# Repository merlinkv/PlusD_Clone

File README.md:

# PlusD Clone

<br />This work is licensed under a <a rel="license" href="http://creativecommons.org/licenses/by-nc-sa/4.0/">Creative Commons Attribution-NonCommercial-ShareAlike 4.0 International License</a>.

* If you remix, transform, or build upon the material, you must distribute your contributions under the same license as the original.
* You may not use the material for commercial purposes.
* You must give appropriate credit, provide a link to the license, and indicate if changes were made. You may do so in any reasonable manner, but not in any way that suggests the licensor endorses you or your use.

This interface is based on the original PlusD (+D) interface from Miles Gordon Technology and the clone designs by @Pachuquin & @alvaroalea.

# ATTENTION

This project was made for the retro community and not for commercial purposes. So only retro hardware forums and individual people can build this project.

THE SALE OF ANY PART OF THIS PROJECT ON EBAY OR OTHER AUCTION SITES IS PROHIBITED

# Note

I take no responsibiltiy for any damage to any equipment that results from the use of this board. USE AT YOUR OWN RISK!

# Original short description

The PlusD (or +D) was a floppy disk and printer interface for the Sinclair ZX Spectrum home computer, developed as a successor to Miles Gordon Technology's earlier product, the DISCiPLE. It runs the GDOS or Uni-Dos operating systems and you can connect up to two 3.5" floppy drives.

The PlusD will allow you to save all your games and serious software to disc at the touch of a button for reloading at any time in the future. With the fastest load and
save times of any disc system available for the Spectrum, the PLUS D will make your computer grow to meet your needs today and tomorrow! In the software arena, many
leading companies are now producing software that is specifically tailored to the PLUS D. But don't worry - you don't have to buy new software to use the PLUS D!
And if some of your software is Microdrive compatible, so much the better! The PLUS D will add a new dimension to all your existing software, greatly enhancing all
your own programs as well!

# August 6, 2025 - PlusD Clone 1.7

* Added Fire2 button on Kempston interface. Now you can play games that are ready for two buttons or modified to add this possibility like on some games modded by @mad3001 at the VDR site: [Games with Fire2](https://www.va-de-retro.com/foros/viewtopic.php?t=12277)

- [Interactive BOM](https://htmlpreview.github.io/?https://github.com/merlinkv/PlusD_Clone/blob/master/ZX_PlusD_Clone_1_7.html)

# PlusD Clone 1.6

My ZX PlusD Clone can be used on all ZX Spectrum computers just using a little switch (you don't need a "fixer" for +2A, +2B or +3 models). Also you can select one of the two ROMs included (GDOS & Uni-Dos -up to four ROMs can be used-) and play almost all games with the integrated Kempston Joystick interface.

# July 30, 2021

* Corrected some IC labels on the board.

# November 25, 2020

* The solder pad used to select the floppy drive controller IC has been removed.
The floppy drive controller IC's that can be used are: WD1772-02-00, WD1772-02-02 & VL1772-02PC
* Some minor changes.

# October 16, 2020

* Resistors, capacitors (except the two electrolytics) & diodes now are SMD 1206
* Some minor changes

# September 25, 2020

* In this version the solder pads to select the READY signal has been removed.
* Now you can fin a connector of 4x2 pins to put the jumpers.
     
     * Upper row: Cable selector (AT or Shugart)
     * Bottom row: READY signal selector, REAL or EMU
      
     See attached pictures.

# July 27, 2020

Tested & working 100%
* In this version of the board the IC 7805 has been removed. The interface power is taken from the + 5V line of the expansion bus.

# July 11, 2020

* Corrected footprint of U2 (W27E257)
* Everything seems to be OK. Ordering 5 PCB's to test.

# July 6, 2020

* Added a SPDT switch ON-ON to select between ZX 48K/128K & +2A/+3
* Inversion of Drive 1 and Drive 2 now is made by a DPDT Switch (ABBA)
* Now the IC12 (L7805) can be placed horizontally
* Relocation of LEDS, NMI and RESET pushbuttons and some IC's
* Added three 3M holes (3.5mm) to facilitate the fixation on a case
* Kempston Joystick connector now is horizontal
* Changed the DIP switch for ROM selection and Joystick ON-OFF for a DIP Switch Piano style.
* Electrolytic capacitors are now SMD

# Notes

Two types can be used as the IC for floppy disk controller: WD1772 (versions 02-00 and 02-02) and VL1772-02PC.
Unfortunately, they are difficult to find at reasonable prices.

The advantages of this interface over the original are:

* 4 Banks of ROM, so you can swap between G+Dos and Unidos, selectable by dip-switches
* Included Fixed for +2A/+3, so can be used in any ZX Spectrum, selection by switch
* Kempston Joystick Interface included, can be disable by dip-switch
* Reset Button
* Posibility of use crossed or plain floppy cable, and invert Drive 1 and Drive 2, very usefull if you have a Gotek and a real floppy.

# Links

* https://www.winuaespanol.com/phpbb3/viewtopic.php?p=7182#p7182
* https://github.com/alvaroalea/plusD-clone
* https://www.va-de-retro.com/foros/viewtopic.php?f=63&t=5561

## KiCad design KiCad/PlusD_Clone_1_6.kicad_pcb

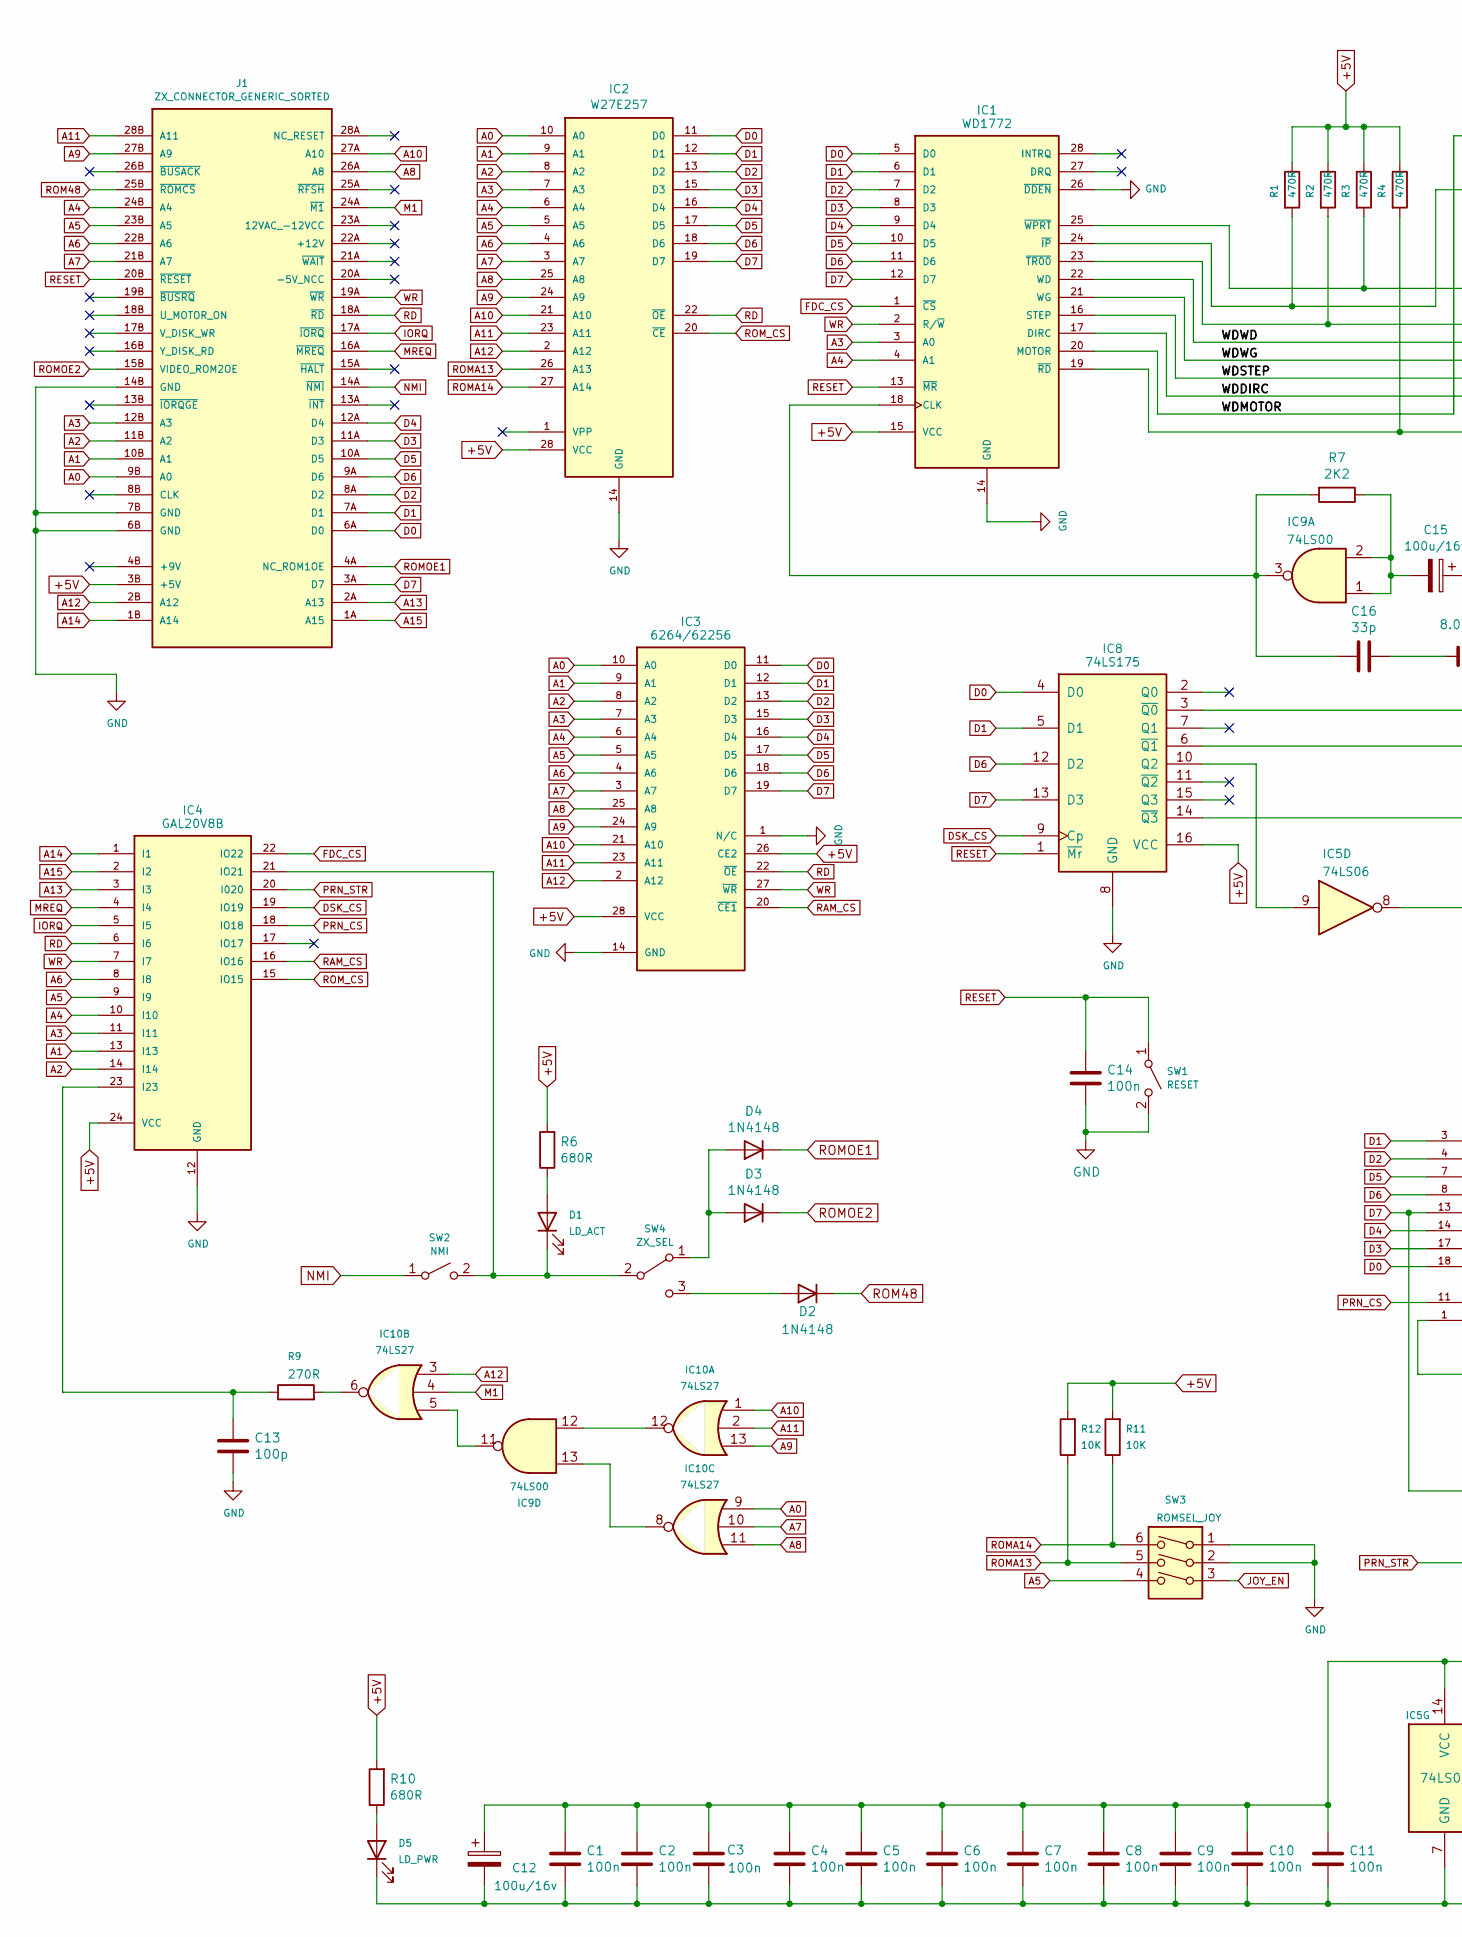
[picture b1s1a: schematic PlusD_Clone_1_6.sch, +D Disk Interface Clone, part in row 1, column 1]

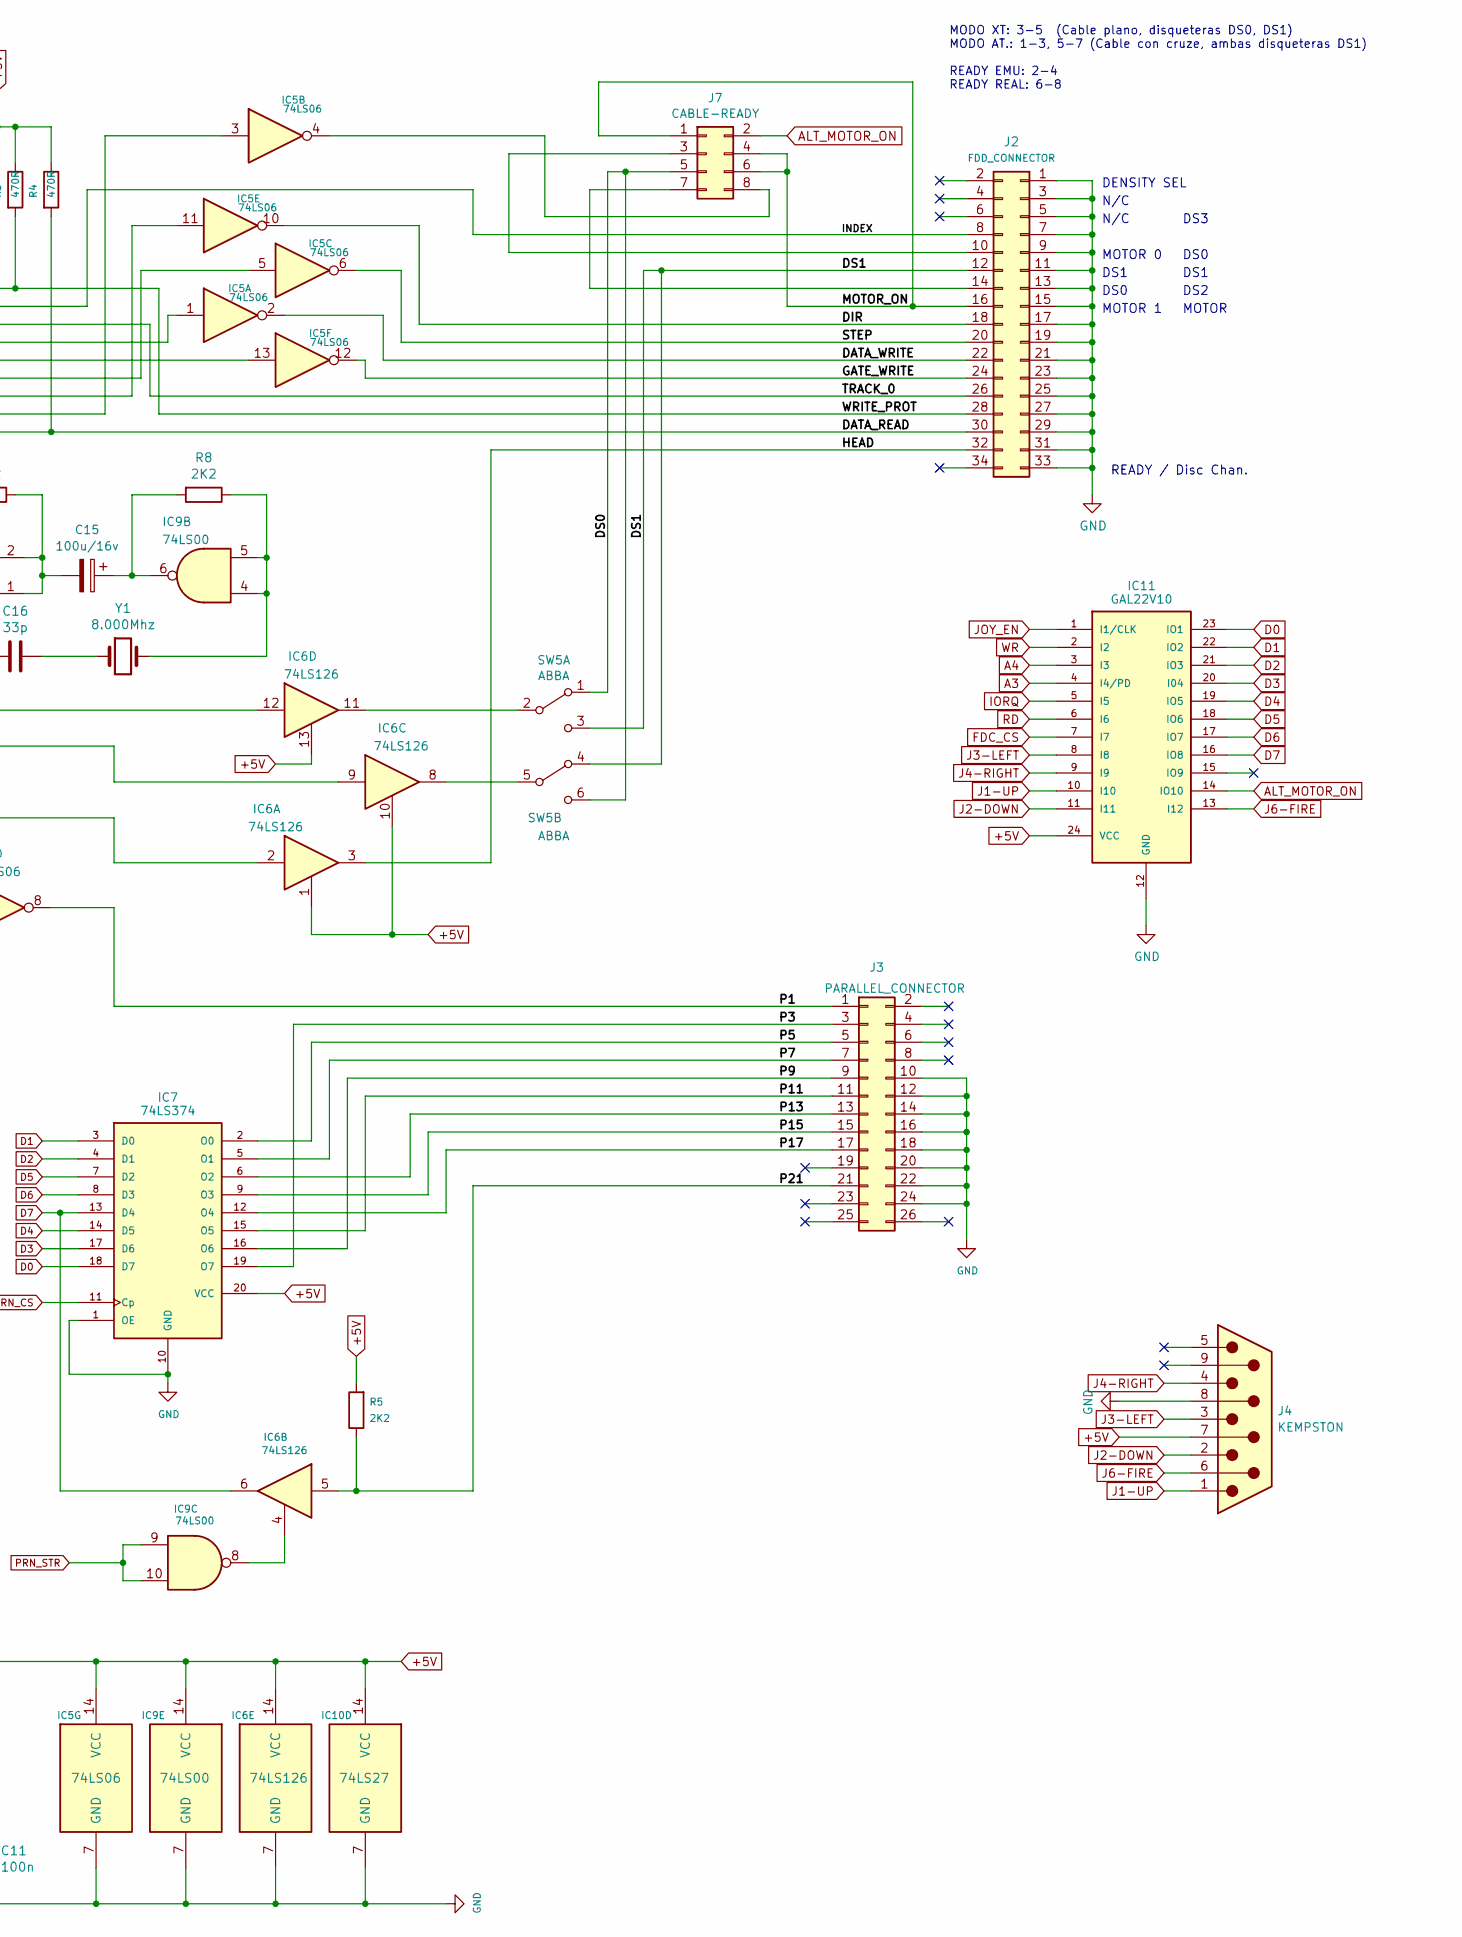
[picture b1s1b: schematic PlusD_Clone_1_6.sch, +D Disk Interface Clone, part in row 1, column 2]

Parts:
C1, C2, C3, C4, C5, C6, C7, C8, C9, C10, C11, C14: 100n; C_1206_3216Metric_Pad1.42x1.75mm_HandSolder
C12, C15: 100u/16v; C_Elec_6.3x5.4
C13: 100p; C_1206_3216Metric_Pad1.42x1.75mm_HandSolder
C16: 33p; C_1206_3216Metric_Pad1.42x1.75mm_HandSolder
D1: LD_ACT; LED_D5.0mm
D2, D3, D4: 1N4148; D_SOD-123
D5: LD_PWR; LED_D5.0mm
IC1: WD1772; DIP-28_W15.24mm_Socket_LongPads
IC2: W27E257; DIP-28_W15.24mm_Socket_LongPads
IC3: 6264/62256; DIP-28_W15.24mm_Socket_LongPads
IC4: GAL20V8B; DIP-24_W7.62mm_Socket_LongPads
IC5: 74LS06; DIP-14_W7.62mm_Socket_LongPads
IC6: 74LS126; DIP-14_W7.62mm_Socket_LongPads
IC7: 74LS374; DIP-20_W7.62mm_Socket_LongPads
IC8: 74LS175; DIP-16_W7.62mm_Socket_LongPads
IC9: 74LS00; DIP-14_W7.62mm_Socket_LongPads
IC10: 74LS27; DIP-14_W7.62mm_Socket_LongPads
IC11: GAL22V10; DIP-24_W7.62mm_Socket_LongPads
J1: ZX_CONNECTOR_GENERIC_SORTED
J2: FDD_CONNECTOR; PinHeader_2x17_P2.54mm_Vertical
J3: PARALLEL_CONNECTOR; PinHeader_2x13_P2.54mm_Vertical
J4: KEMPSTON; DSUB-9_Male_Horizontal_P2.77x2.84mm_EdgePinOffset4.94mm_Hou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
J7: CABLE-READY; PinHeader_2x04_P2.54mm_Horizontal
R1, R2, R3, R4: 470R; R_1206_3216Metric_Pad1.42x1.75mm_HandSolder
R5, R7, R8: 2K2; R_1206_3216Metric_Pad1.42x1.75mm_HandSolder
R6, R10: 680R; R_1206_3216Metric_Pad1.42x1.75mm_HandSolder
R9: 270R; R_1206_3216Metric_Pad1.42x1.75mm_HandSolder
R11, R12: 10K; R_1206_3216Metric_Pad1.42x1.75mm_HandSolder
SW1: RESET; SW_PUSH_6mm
SW2: NMI; SW_PUSH_6mm
SW3: ROMSEL_JOY; SW_DIP_SPSTx03_Piano_10.8x9.18mm_W7.62mm_P2.54mm
SW4: ZX_SEL; SW_CuK_OS102011MA1QN1_SPDT_Angled
SW5: ABBA; SW_CuK_JS202011AQN_DPDT_Angled
Y1: 8.000Mhz; Crystal_HC18-U_Vertical

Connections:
+5V: C1.2, C2.2, C3.2, C4.2, C5.2, C6.2, C7.2, C8.2, C9.2, C10.2, C11.2, C12.1, IC1.15 (VCC), IC2.28 (VCC), IC3.26 (CE2), IC3.28 (VCC), IC4.24 (VCC), IC5.14 (VCC), IC6.1, IC6.10, IC6.13, IC6.14 (VCC), IC7.20 (VCC), IC8.16 (VCC), IC9.14 (VCC), IC10.14 (VCC), IC11.24 (VCC), J1.3B (+5V), J4.7, R1.1, R2.1, R3.1, R4.1, R5.2, R6.2, R10.2, R11.2, R12.2
/DATA_READ: IC1.19 (~RD), J2.30, R4.2
/DATA_WRITE: IC5.2, J2.22
/DIR: IC5.10, J2.18
/DS0: J7.5, SW5.1 (A), SW5.6 (C)
/DS1: J2.12, SW5.3 (C), SW5.4 (A)
/GATE_WRITE: IC5.12, J2.24
/HEAD: IC6.3, J2.32
/INDEX: IC1.24 (~IP), J2.8, R1.2
/MOTOR_ON: J2.16, J7.1, J7.4, J7.6
/P1: IC5.8, J3.1
/P3: IC7.19 (O7), J3.3
/P5: IC7.2 (O0), J3.5
/P7: IC7.5 (O1), J3.7
/P9: IC7.16 (O6), J3.9
/P11: IC7.15 (O5), J3.11
/P13: IC7.6 (O2), J3.13
/P15: IC7.9 (O3), J3.15
/P17: IC7.12 (O4), J3.17
/P21: IC6.5, J3.21, R5.1
/STEP: IC5.6, J2.20
/TRACK_0: IC1.23 (~TR00), J2.26, R2.2
/WDDIRC: IC1.17 (DIRC), IC5.11
/WDMOTOR: IC1.20 (MOTOR), IC5.3
/WDSTEP: IC1.16 (STEP), IC5.5
/WDWD: IC1.22 (WD), IC5.1
/WDWG: IC1.21 (WG), IC5.13
/WRITE_PROT: IC1.25 (~WPRT), J2.28, R3.2
A0: IC2.10 (A0), IC3.10 (A0), IC10.9, J1.9B (A0)
A1: IC2.9 (A1), IC3.9 (A1), IC4.13 (I13), J1.10B (A1)
A2: IC2.8 (A2), IC3.8 (A2), IC4.14 (I14), J1.11B (A2)
A3: IC1.3 (A0), IC2.7 (A3), IC3.7 (A3), IC4.11 (I11), IC11.4 (I4/PD), J1.12B (A3)
A4: IC1.4 (A1), IC2.6 (A4), IC3.6 (A4), IC4.10 (I10), IC11.3 (I3), J1.24B (A4)
A5: IC2.5 (A5), IC3.5 (A5), IC4.9 (I9), J1.23B (A5), SW3.4
A6: IC2.4 (A6), IC3.4 (A6), IC4.8 (I8), J1.22B (A6)
A7: IC2.3 (A7), IC3.3 (A7), IC10.10, J1.21B (A7)
A8: IC2.25 (A8), IC3.25 (A8), IC10.11, J1.26A (A8)
A9: IC2.24 (A9), IC3.24 (A9), IC10.13, J1.27B (A9)
A10: IC2.21 (A10), IC3.21 (A10), IC10.1, J1.27A (A10)
A11: IC2.23 (A11), IC3.23 (A11), IC10.2, J1.28B (A11)
A12: IC2.2 (A12), IC3.2 (A12), IC10.3, J1.2B (A12)
A13: IC4.3 (I3), J1.2A (A13)
A14: IC4.1 (I1), J1.1B (A14)
A15: IC4.2 (I2), J1.1A (A15)
ALT_MOTOR_ON: IC11.14 (IO10), J7.2
D0: IC1.5 (D0), IC2.11 (D0), IC3.11 (D0), IC7.18 (D7), IC8.4 (D0), IC11.23 (IO1), J1.6A (D0)
D1: IC1.6 (D1), IC2.12 (D1), IC3.12 (D1), IC7.3 (D0), IC8.5 (D1), IC11.22 (IO2), J1.7A (D1)
D2: IC1.7 (D2), IC2.13 (D2), IC3.13 (D2), IC7.4 (D1), IC11.21 (IO3), J1.8A (D2)
D3: IC1.8 (D3), IC2.15 (D3), IC3.15 (D3), IC7.17 (D6), IC11.20 (I04), J1.11A (D3)
D4: IC1.9 (D4), IC2.16 (D4), IC3.16 (D4), IC7.14 (D5), IC11.19 (IO5), J1.12A (D4)
D5: IC1.10 (D5), IC2.17 (D5), IC3.17 (D5), IC7.7 (D2), IC11.18 (IO6), J1.10A (D5)
D6: IC1.11 (D6), IC2.18 (D6), IC3.18 (D6), IC7.8 (D3), IC8.12 (D2), IC11.17 (IO7), J1.9A (D6)
D7: IC1.12 (D7), IC2.19 (D7), IC3.19 (D7), IC6.6, IC7.13 (D4), IC8.13 (D3), IC11.16 (IO8), J1.3A (D7)
DSK_CS: IC4.19 (IO19), IC8.9 (Cp)
FDC_CS: IC1.1 (~CS), IC4.22 (IO22), IC11.7 (I7)
GND: C1.1, C2.1, C3.1, C4.1, C5.1, C6.1, C7.1, C8.1, C9.1, C10.1, C11.1, C12.2, C13.1, C14.1, D5.1 (K), IC1.14 (GND), IC1.26 (~DDEN), IC2.14 (GND), IC3.1 (N/C), IC3.14 (GND), IC4.12 (GND), IC5.7 (GND), IC6.7 (GND), IC7.1 (OE), IC7.10 (GND), IC8.8 (GND), IC9.7 (GND), IC10.7 (GND), IC11.12 (GND), J1.6B (GND), J1.7B (GND), J1.14B (GND), J2.1, J2.3, J2.5, J2.7, J2.9, J2.11, J2.13, J2.15, J2.17, J2.19, J2.21, J2.23, J2.25, J2.27, J2.29, J2.31, J2.33, J3.10, J3.12, J3.14, J3.16, J3.18, J3.20, J3.22, J3.24, J4.8, SW1.2 (B), SW3.1, SW3.2
IORQ: IC4.5 (I5), IC11.5 (I5), J1.17A (~IORQ)
J1-UP: IC11.10 (I10), J4.1
J2-DOWN: IC11.11 (I11), J4.2
J3-LEFT: IC11.8 (I8), J4.3
J4-RIGHT: IC11.9 (I9), J4.4
J6-FIRE: IC11.13 (I12), J4.6
JOY_EN: IC11.1 (I1/CLK), SW3.3
M1: IC10.4, J1.24A (~M1)
MREQ: IC4.4 (I4), J1.16A (~MREQ)
NMI: J1.14A (~NMI), SW2.1 (A)
unnamed: C13.2, IC4.23 (I23), R9.1
unnamed: C15.1, IC9.6, R8.2
unnamed: C15.2, IC9.1, IC9.2, R7.1
unnamed: C16.1, Y1.1
unnamed: C16.2, IC1.18 (CLK), IC9.3, R7.2
unnamed: D1.1 (K), IC4.21 (IO21), SW2.2 (B), SW4.2 (B)
unnamed: D1.2 (A), R6.1
unnamed: D2.2 (A), SW4.3 (C)
unnamed: D3.2 (A), D4.2 (A), SW4.1 (A)
unnamed: D5.2 (A), R10.1
unnamed: IC5.4, J7.8
unnamed: IC5.9, IC8.10 (Q2)
unnamed: IC6.2, IC8.14 (~Q3)
unnamed: IC6.4, IC9.8
unnamed: IC6.8, SW5.5 (B)
unnamed: IC6.9, IC8.6 (~Q1)
unnamed: IC6.11, SW5.2 (B)
unnamed: IC6.12, IC8.3 (~Q0)
unnamed: IC9.4, IC9.5, R8.1, Y1.2
unnamed: IC9.11, IC10.5
unnamed: IC10.6, R9.2
unnamed: IC9.13, IC10.8
unnamed: IC9.12, IC10.12
unnamed: J2.10, J7.3
unnamed: J2.14, J7.7
PRN_CS: IC4.18 (IO18), IC7.11 (Cp)
PRN_STR: IC4.20 (I020), IC9.9, IC9.10
RAM_CS: IC3.20 (~CE1), IC4.16 (IO16)
RD: IC2.22 (~OE), IC3.22 (~OE), IC4.6 (I6), IC11.6 (I6), J1.18A (~RD)
RESET: C14.2, IC1.13 (~MR), IC8.1 (~Mr), J1.20B (~RESET), SW1.1 (A)
ROM48: D2.1 (K), J1.25B (~ROMCS)
ROMA13: IC2.26 (A13), R12.1, SW3.5
ROMA14: IC2.27 (A14), R11.1, SW3.6
ROMOE1: D4.1 (K), J1.4A (NC_ROM1OE)
ROMOE2: D3.1 (K), J1.15B (VIDEO_ROM2OE)
ROM_CS: IC2.20 (~CE), IC4.15 (IO15)
WR: IC1.2 (R/~W), IC3.27 (~WR), IC4.7 (I7), IC11.2 (I2), J1.19A (~WR)

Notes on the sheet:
READY / Disc Chan.
DENSITY SEL
N/C
MOTOR 1
DS0
DS1
MOTOR 0
MOTOR
DS2
DS0
DS3
MODO XT: 3-5 (Cable plano, disqueteras DS0, DS1) MODO AT.: 1-3, 5-7 (Cable con cruze, ambas disqueteras DS1) READY EMU: 2-4 READY REAL: 6-8

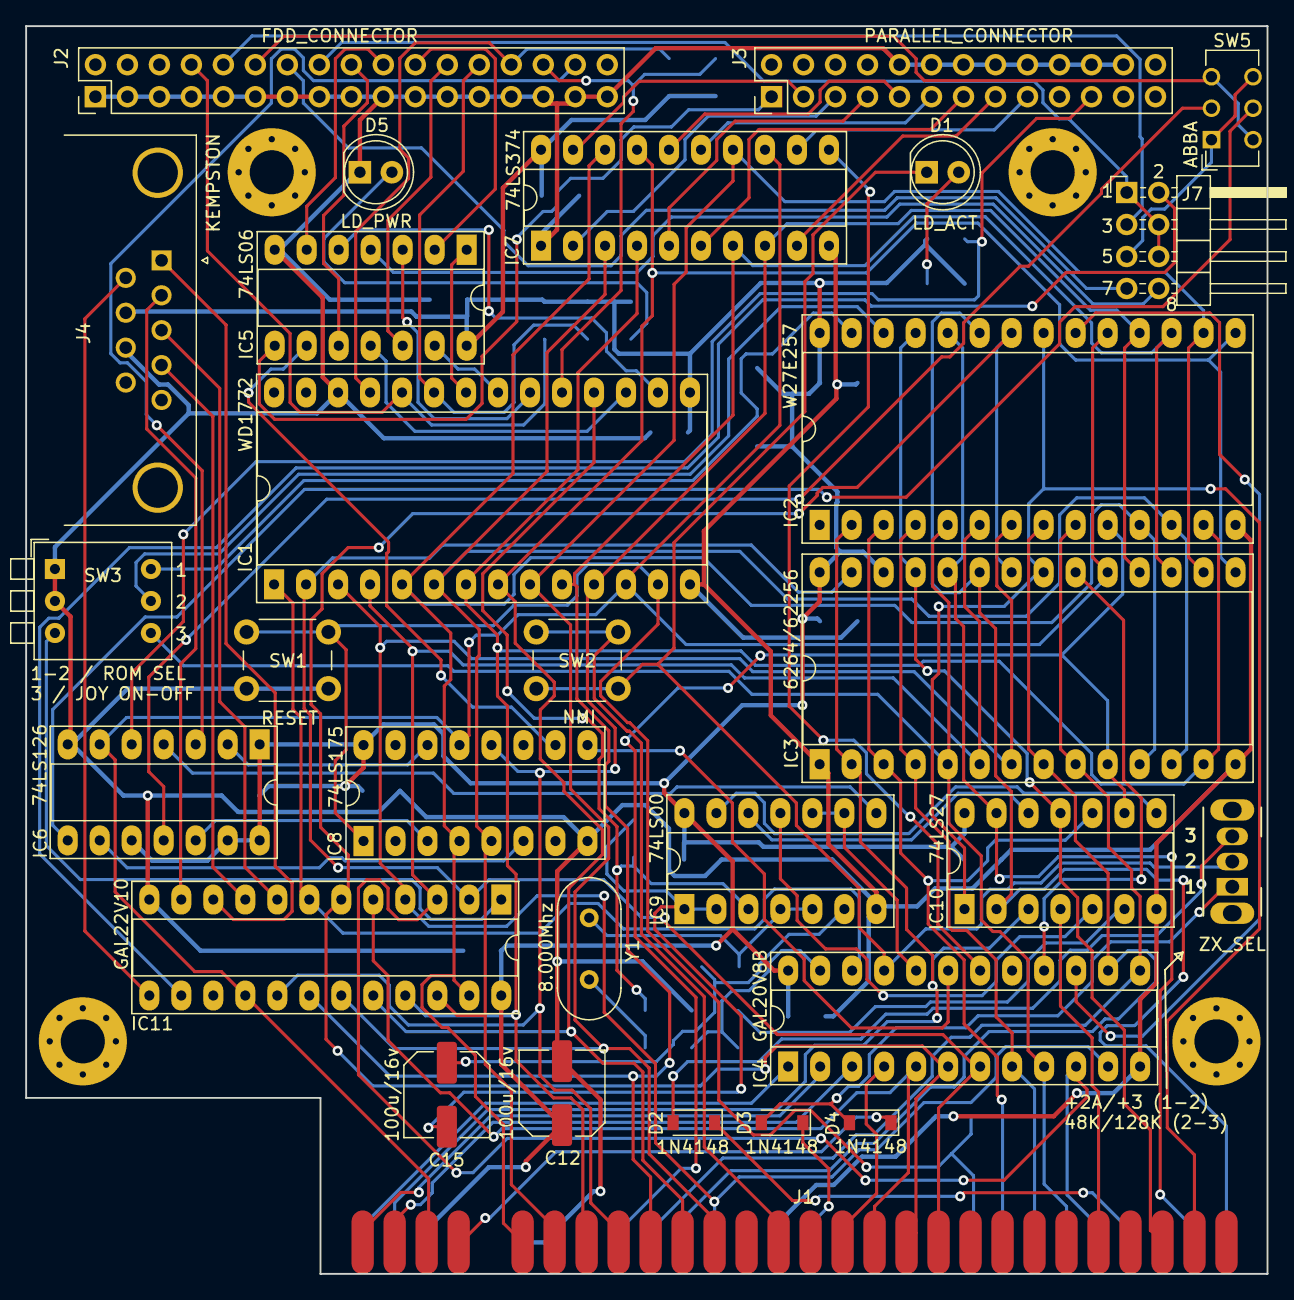
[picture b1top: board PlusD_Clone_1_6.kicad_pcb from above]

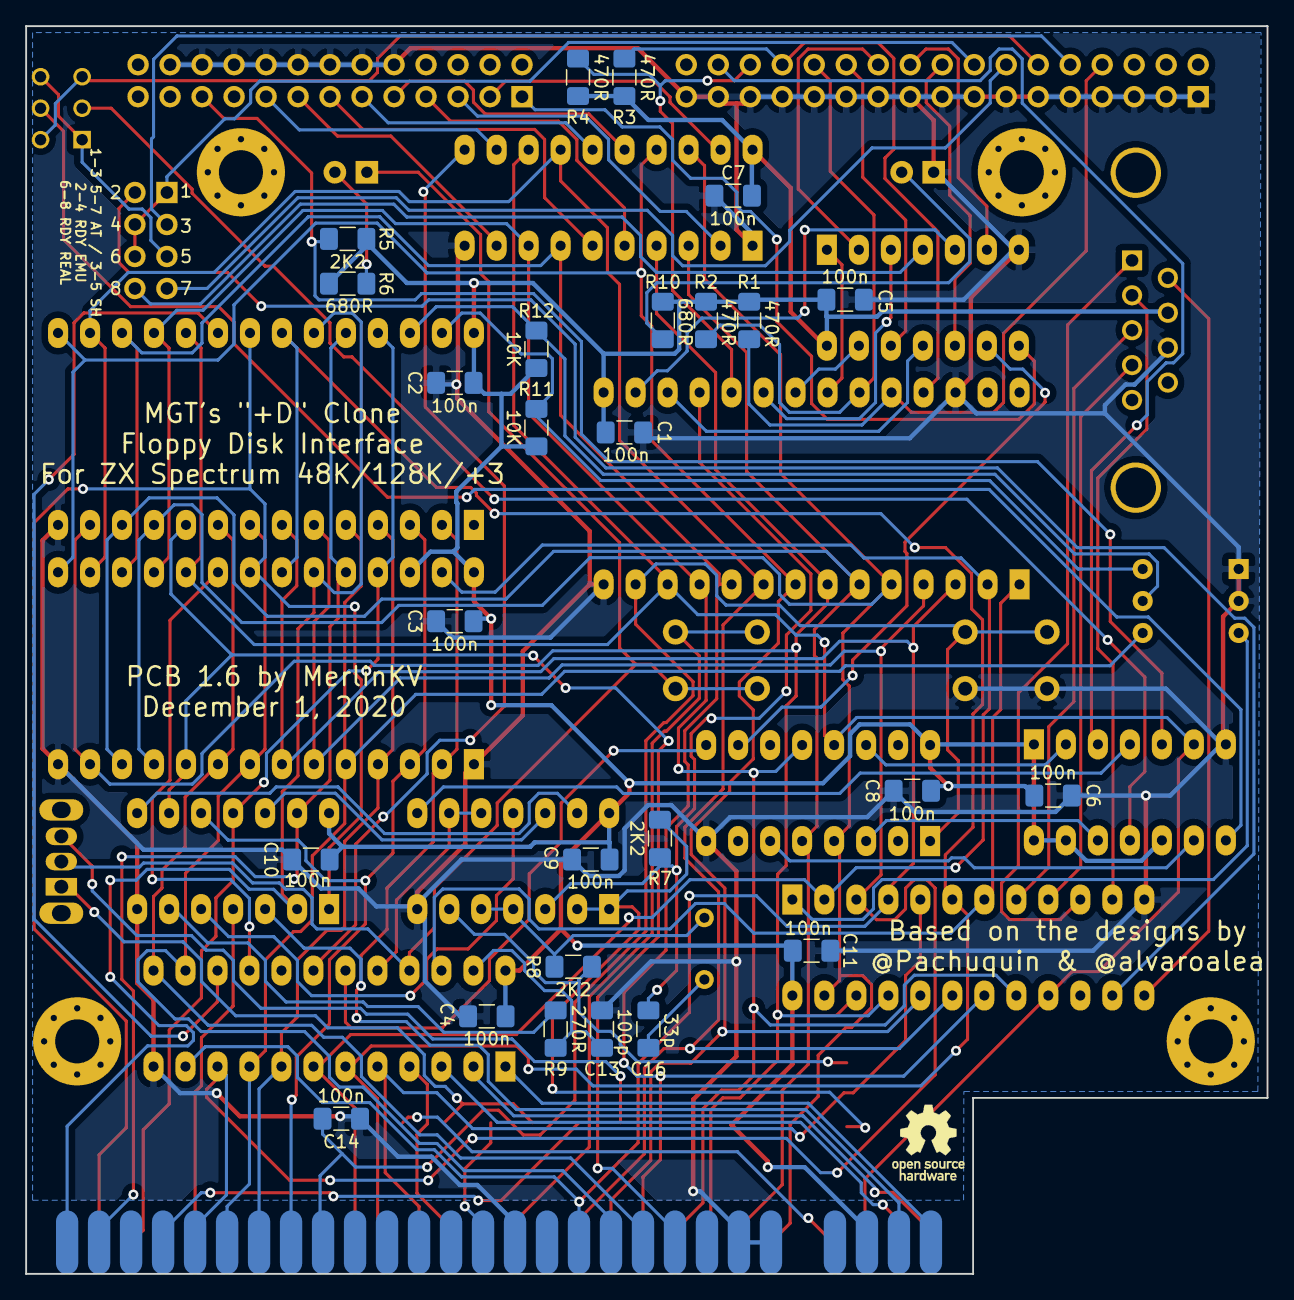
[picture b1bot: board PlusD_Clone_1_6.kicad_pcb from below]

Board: 2 copper layers, 98.6 x 99.1 mm, 60 parts (27 on the bottom side), 103 nets.

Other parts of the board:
HOLE1, HOLE2, HOLE3, HOLE4: MountingHole_3.5mm_Pad_Via
LOGO1: OSHW-Logo_5.7x6mm_SilkScreen

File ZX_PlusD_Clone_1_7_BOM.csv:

"Id";"Designator";"Footprint";"Quantity";"Designation";"Supplier and ref";
1;"J4";"DSUB-9_Male_Horizontal_P2.77x2.84mm_EdgePinOffset4.94mm_Housed_MountingHolesOffset7.48mm";1;"Kempston";;;
2;"SW4";"SW_CuK_OS102011MA1QN1_SPDT_Angled";1;"ZX_SEL";;;
3;"IC10";"DIP-14_W7.62mm_Socket";1;"74LS27";;;
4;"IC9";"DIP-14_W7.62mm_Socket";1;"74LS00";;;
5;"IC6";"DIP-14_W7.62mm_Socket";1;"74LS126";;;
6;"D5";"LED_D3.0mm";1;"LD_PWR";;;
7;"SW3";"SW_DIP_SPSTx03_Piano_10.8x9.18mm_W7.62mm_P2.54mm";1;"ROMSEL_JOY";;;
8;"Y1";"Crystal_HC18-U_Vertical";1;"8.000Mhz";;;
9;"D1";"LED_D3.0mm";1;"LD_ACT";;;
10;"IC5";"DIP-14_W7.62mm_Socket";1;"74LS06";;;
11;"J3";"PinHeader_2x13_P2.54mm_Vertical";1;"PARALLEL_CONNECTOR";;;
12;"J1";"ZX_CONNECTOR_GENERIC_SORTED";1;"ZX_CONNECTOR_GENERIC_SORTED";;;
13;"IC1";"DIP-28_W15.24mm_Socket";1;"WD1772";;;
14;"IC3";"DIP-28_W15.24mm_Socket";1;"6264/62256";;;
15;"IC4";"DIP-24_W7.62mm_Socket";1;"GAL20V8B";;;
16;"IC8";"DIP-16_W7.62mm_Socket";1;"74LS175";;;
17;"IC7";"DIP-20_W7.62mm_Socket";1;"74LS374";;;
18;"SW1";"SW_PUSH_6mm";1;"RESET";;;
19;"SW2";"SW_PUSH_6mm";1;"NMI";;;
20;"IC11";"DIP-24_W7.62mm_Socket";1;"GAL22V10";;;
21;"IC2";"DIP-28_W15.24mm_Socket";1;"W27E257";;;
22;"SW5";"SW_CK_JS202011AQN_DPDT_Angled";1;"ABBA";;;
23;"C15,C12";"C_Elec_6.3x5.4";2;"100u/16v";;;
24;"J7";"PinHeader_2x04_P2.54mm_Horizontal";1;"CABLE-READY";;;
25;"D2,D3,D4";"D_SOD-123";3;"1N4148";;;
26;"J2";"PinHeader_2x17_P2.54mm_Vertical";1;"FDD_CONNECTOR";;;
27;"C16";"C_1206_3216Metric_Pad1.33x1.80mm_HandSolder";1;"33p";;;
28;"R9";"R_1206_3216Metric_Pad1.30x1.75mm_HandSolder";1;"270R";;;
29;"R6,R10";"R_1206_3216Metric_Pad1.30x1.75mm_HandSolder";2;"680R";;;
30;"R12,R11";"R_1206_3216Metric_Pad1.30x1.75mm_HandSolder";2;"10K";;;
31;"R7,R8,R5";"R_1206_3216Metric_Pad1.30x1.75mm_HandSolder";3;"2K2";;;
32;"C13";"C_1206_3216Metric_Pad1.33x1.80mm_HandSolder";1;"100p";;;
33;"C14,C1,C4,C5,C6,C7,C8,C9,C10,C11,C2,C3";"C_1206_3216Metric_Pad1.33x1.80mm_HandSolder";12;"100n";;;
34;"R1,R2,R4,R3";"R_1206_3216Metric_Pad1.30x1.75mm_HandSolder";4;"470R";;;
